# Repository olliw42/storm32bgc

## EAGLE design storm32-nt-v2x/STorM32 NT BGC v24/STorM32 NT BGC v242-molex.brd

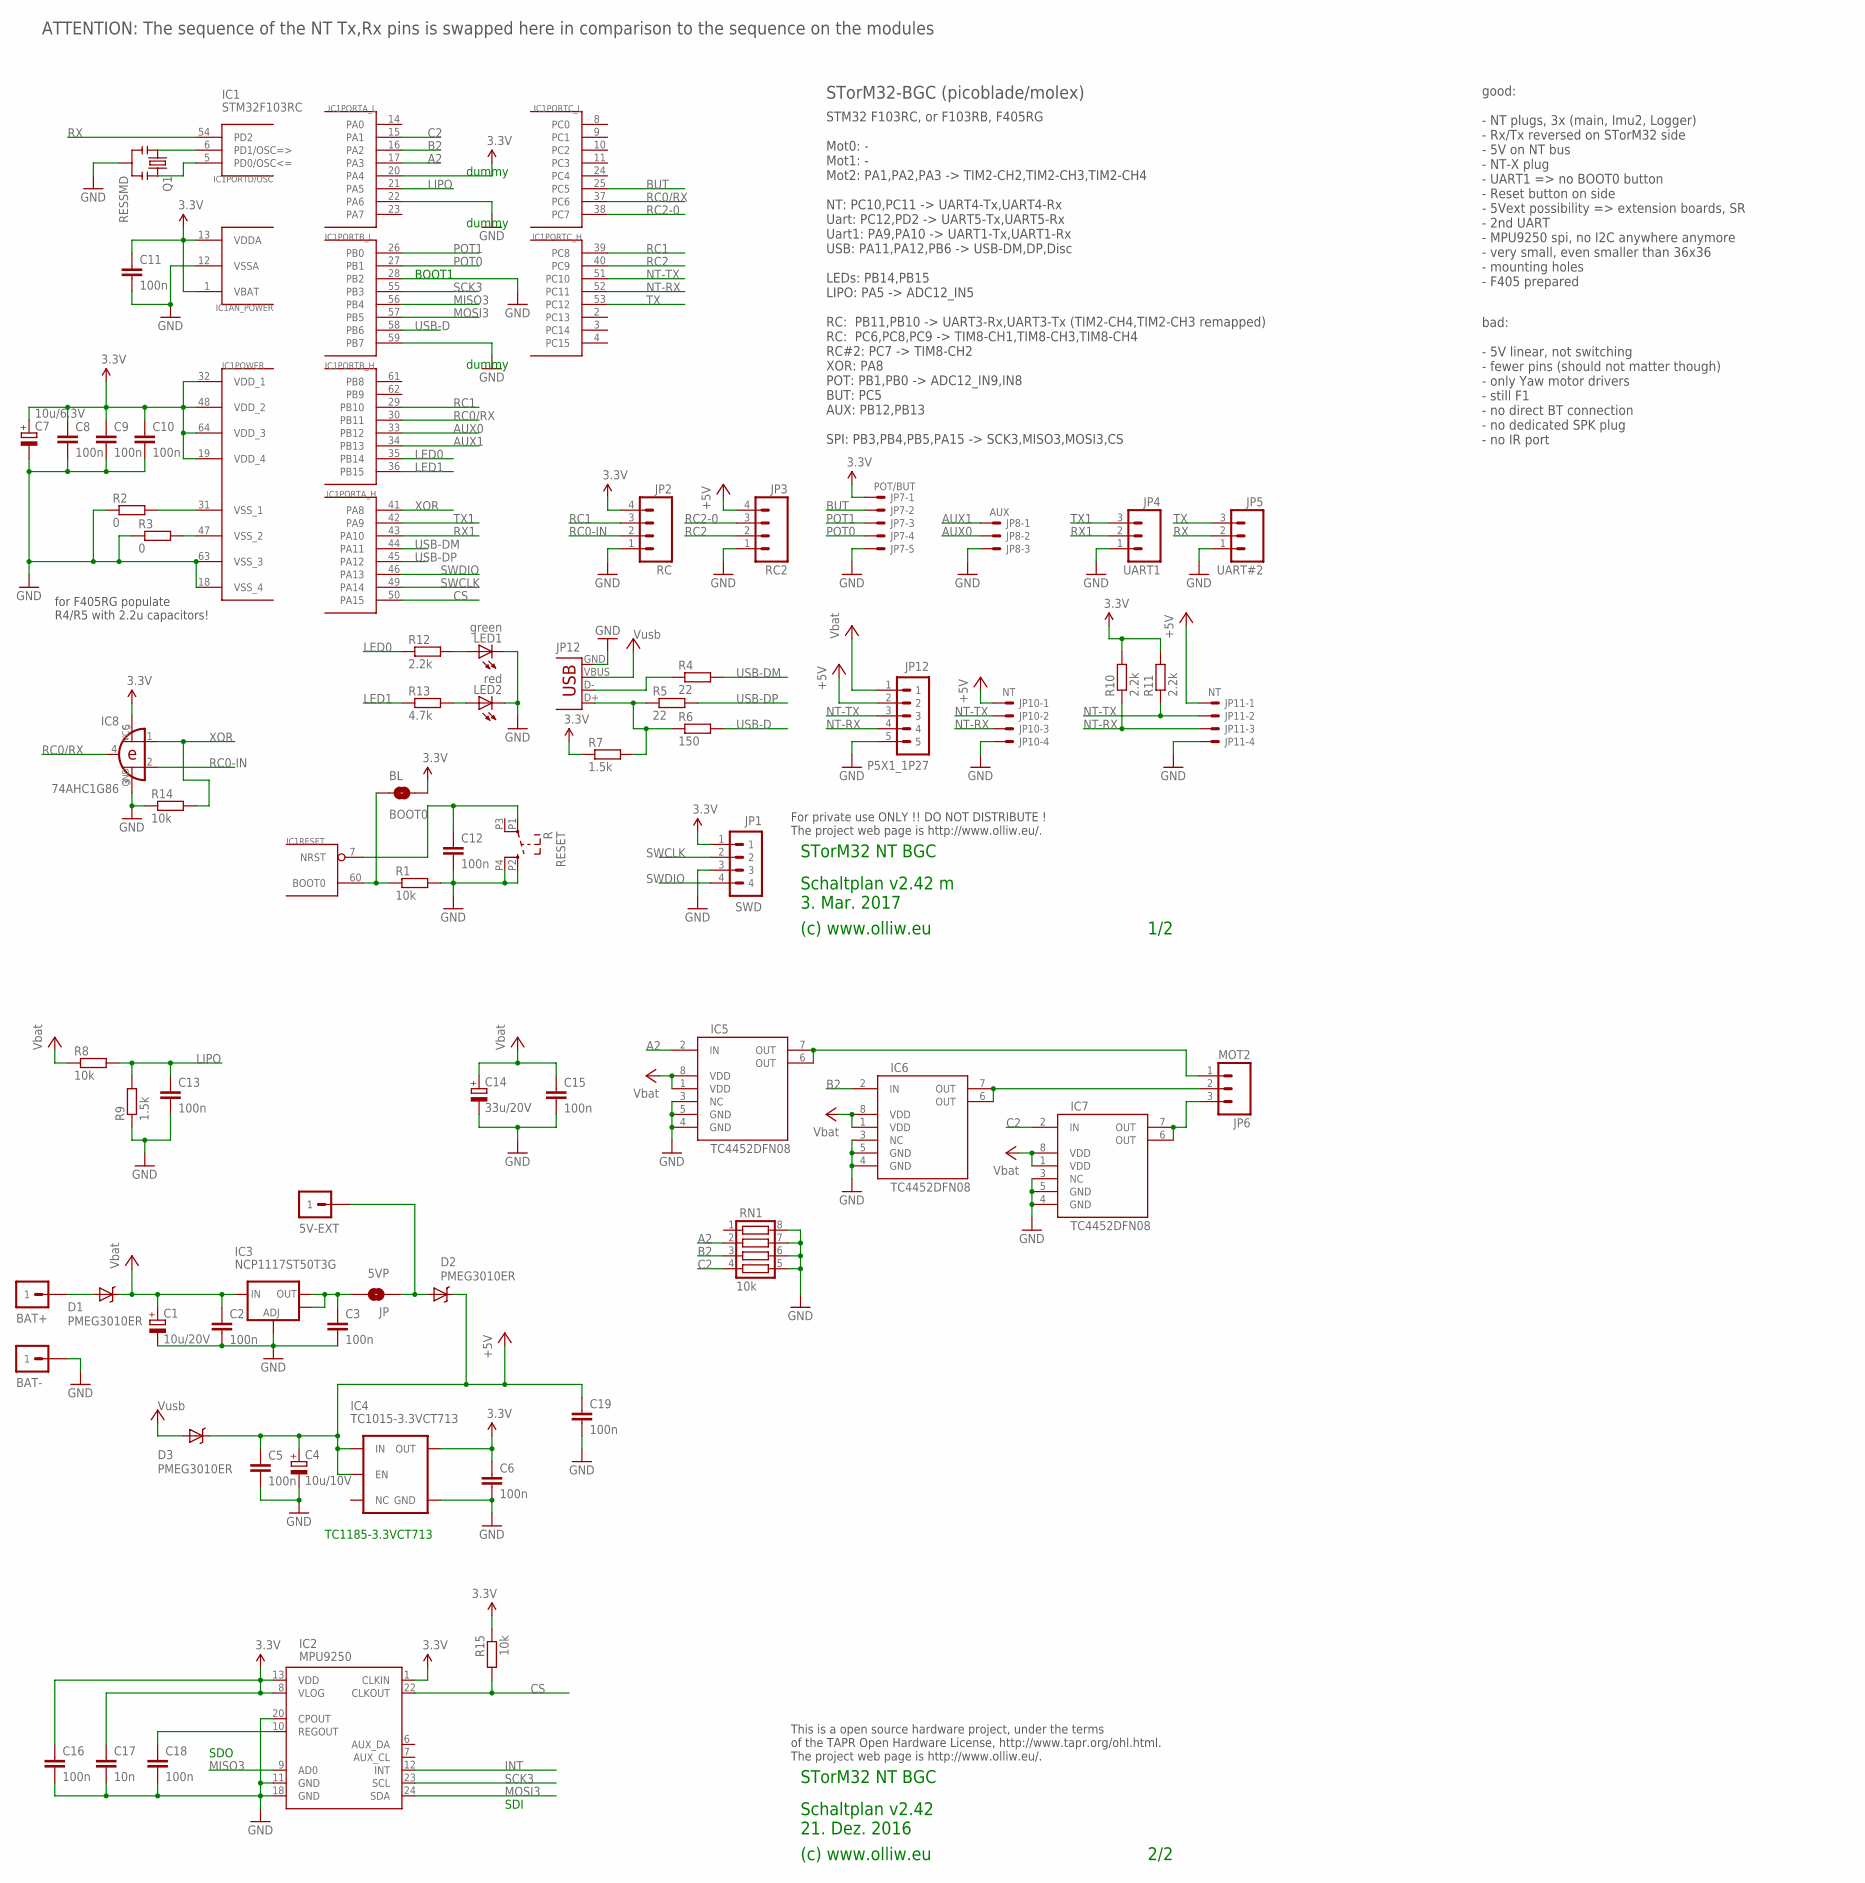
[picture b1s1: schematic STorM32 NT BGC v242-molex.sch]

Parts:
5V-EXT: M1X1; 1X1_WITHOUT
BAT+: M1X1; 1X1_WITHOUT
BAT-: M1X1; 1X1_WITHOUT
BL: BOOT0; SJ_2S-NO
C1: 10u/20V; SMC_B
C2, C5, C15: 100n; C0603
C3, C6, C8, C9, C10, C11, C12, C13, C16, C18, C19: 100n; C0402
C4: 10u/10V; SMC_A
C7: 10u/6.3V; SMC_A
C14: 33u/20V; SMC_C
C17: 10n; C0402
D1, D2, D3: PMEG3010ER; SOD123W-DIODE
IC1: STM32F103RCT6; TQFP64
IC2: MPU9250; QFN-24-3X3
IC3: NCP1117ST50T3G; SOT223
IC4: TC1015-3.3VCT713; SOT23-5
IC5, IC6, IC7: TC4452DFN08; DFN8
IC8: 74AHC1G86; SOT23-5-VER1
JP: 5VP; SJ_2S-NO
JP1: SWD; 4X1_1P27_OCT_BILEX
JP2: RC; 1X04_NO_SILK
JP3: RC2; 1X04_NO_SILK
JP4: UART1; 1X03_NO_SILK
JP5: UART#2; 1X03_NO_SILK
JP6: MOT2; 1X03_NO_SILK
JP7: POT/BUT; SM05B-SRSS-TB
JP8: AUX; SM03B-SRSS-TB
JP10, JP11: NT; SM04B-SRSS-TB
JP12: P5X1_1P27; MOLEX-53261-05-SMD-FLAT
LED1: green; CHIPLED_0603
LED2: red; CHIPLED_0603
Q1: RESSMD; RESONATOR-SMD
R1, R8, R14, R15: 10k; R0402
R2, R3: 0; R0402
R4, R5: 22; R0402
R6: 150; R0402
R7, R9: 1.5k; R0402
R10, R11, R12: 2.2k; R0402
R13: 4.7k; R0402
RESET: R; TACTILE-SWITCH-SMD-RIGHT-TL1014
RN1: 10k; CTS742C083
USB: USB-MICROB

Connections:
3.3V: BL.2, C6.1, C7.+, C8.1, C9.1, C10.1, C11.1, C16.1, C17.1, IC1.1 (VBAT), IC1.13 (VDDA), IC1.19 (VDD_4), IC1.20 (PA4), IC1.32 (VDD_1), IC1.48 (VDD_2), IC1.64 (VDD_3), IC2.1 (CLKIN), IC2.8 (VLOG), IC2.13 (VDD), IC4.5 (OUT), IC8.5 (VCC), JP1.1, JP2.4, JP7.1, R7.1, R10.2, R11.2, R15.1
5V-EXT: 5V-EXT.1, D2.A, JP.1
5V-LDO: C3.1, IC3.2 (OUT), IC3.4 (OUT), JP.2
+5V: C4.+, C5.1, C19.1, D2.C, D3.C, IC4.1 (IN), IC4.3 (EN), JP3.4, JP10.1, JP11.1, JP12.2
A2: IC1.17 (PA3), IC5.2 (IN), RN1.2
AUX0: IC1.33 (PB12), JP8.2
AUX1: IC1.34 (PB13), JP8.1
B2: IC1.16 (PA2), IC6.2 (IN), RN1.3
BATP: BAT+.1, D1.A
BOOT0: BL.1, IC1.60 (BOOT0), R1.1
BUT: IC1.25 (PC5), JP7.2
C2: IC1.15 (PA1), IC7.2 (IN), RN1.4
CS: IC1.50 (PA15), IC2.22 (CLKOUT), R15.2
GND: BAT-.1, C1.-, C2.2, C3.2, C4.-, C5.2, C6.2, C7.-, C8.2, C9.2, C10.2, C11.2, C12.2, C13.2, C14.-, C15.2, C16.2, C17.2, C18.2, C19.2, IC1.12 (VSSA), IC1.18 (VSS_4), IC1.22 (PA6), IC1.28 (PB2), IC1.59 (PB7), IC1.63 (VSS_3), IC2.11 (GND), IC2.18 (GND), IC2.20 (CPOUT), IC3.1 (ADJ), IC4.2 (GND), IC5.3 (NC), IC5.4 (GND), IC5.5 (GND), IC6.3 (NC), IC6.4 (GND), IC6.5 (GND), IC7.3 (NC), IC7.4 (GND), IC7.5 (GND), IC8.3 (GND), JP1.3, JP2.1, JP3.1, JP4.1, JP5.1, JP7.5, JP8.3, JP10.4, JP11.4, JP12.5, LED1.C, LED2.C, Q1.2, R1.2, R2.1, R3.1, R9.1, R14.1, RESET.P2 (1), RESET.P4 (2), RN1.5, RN1.6, RN1.7, RN1.8, USB.GND
INT: IC2.12 (INT)
LED0: IC1.35 (PB14), R12.1
LED1: IC1.36 (PB15), R13.1
LIPO: C13.1, IC1.21 (PA5), R8.2, R9.2
M2A: IC5.6 (OUT), IC5.7 (OUT), JP6.1
M2B: IC6.6 (OUT), IC6.7 (OUT), JP6.2
M2C: IC7.6 (OUT), IC7.7 (OUT), JP6.3
MISO3: IC1.56 (PB4), IC2.9 (AD0)
MOSI3: IC1.57 (PB5), IC2.24 (SDA)
unnamed: C18.1, IC2.10 (REGOUT)
unnamed: LED1.A, R12.2
unnamed: LED2.A, R13.2
unnamed: IC1.47 (VSS_2), R3.2
unnamed: IC1.5 (PD0/OSC<=), Q1.3
unnamed: IC1.6 (PD1/OSC=>), Q1.1
unnamed: R4.1, USB.D-
unnamed: R5.1, R6.1, R7.2, USB.D+
unnamed: IC1.31 (VSS_1), R2.2
NRST: C12.1, IC1.7 (NRST), RESET.P1 (3)
NT-RX: IC1.52 (PC11), JP10.3, JP11.3, JP12.4, R10.1
NT-TX: IC1.51 (PC10), JP10.2, JP11.2, JP12.3, R11.1
POT0: IC1.27 (PB1), JP7.4
POT1: IC1.26 (PB0), JP7.3
RC0-IN: IC8.2 (I1), JP2.2
RC0/RX: IC1.30 (PB11), IC1.37 (PC6), IC8.4 (O)
RC1: IC1.29 (PB10), IC1.39 (PC8), JP2.3
RC2: IC1.40 (PC9), JP3.2
RC2-0: IC1.38 (PC7), JP3.3
RX: IC1.54 (PD2), JP5.2
RX1: IC1.43 (PA10), JP4.2
SCK3: IC1.55 (PB3), IC2.23 (SCL)
SWCLK: IC1.49 (PA14), JP1.2
SWDIO: IC1.46 (PA13), JP1.4
TX: IC1.53 (PC12), JP5.3
TX1: IC1.42 (PA9), JP4.3
USB-D: IC1.58 (PB6), R6.2
USB-DM: IC1.44 (PA11), R4.2
USB-DP: IC1.45 (PA12), R5.2
VCC: C1.+, C2.1, C14.+, C15.1, D1.C, IC3.3 (IN), IC5.1 (VDD), IC5.8 (VDD), IC6.1 (VDD), IC6.8 (VDD), IC7.1 (VDD), IC7.8 (VDD), JP12.1, R8.1
VUSB: D3.A, USB.VBUS
XOR: IC1.41 (PA8), IC8.1 (I0), R14.2

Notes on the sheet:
(c) www.olliw.eu
STorM32 NT BGC
For private use ONLY !! DO NOT DISTRIBUTE ! The project web page is http://www.olliw.eu/.
STM32 F103RC, or F103RB, F405RG Mot0: - Mot1: - Mot2: PA1,PA2,PA3 -> TIM2-CH2,TIM2-CH3,TIM2-CH4 NT: PC10,PC11 -> UART4-Tx,UART4-Rx Uart: PC12,PD2 -> UART5-Tx,UART5-Rx Uart1: PA9,PA10 -> UART1-Tx,UART1-Rx USB: PA11,PA12,PB6 -> USB-DM,DP,Disc LEDs: PB14,PB15 LIPO: PA5 -> ADC12_IN5 RC: PB11,PB10 -> UA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
Schaltplan v2.42 21. Dez. 2016
This is a open source hardware project, under the terms of the TAPR Open Hardware License, http://www.tapr.org/ohl.html. The project web page is http://www.olliw.eu/.
STM32F103RC
STorM32-BGC (picoblade/molex)
for F405RG populate R4/R5 with 2.2u capacitors!
1/2
2/2
IC1
JP12
ATTENTION: The sequence of the NT Tx,Rx pins is swapped here in comparison to the sequence on the modules
SDO
SDI
BOOT1
TC1185-3.3VCT713
good: - NT plugs, 3x (main, Imu2, Logger) - Rx/Tx reversed on STorM32 side - 5V on NT bus - NT-X plug - UART1 => no BOOT0 button - Reset button on side - 5Vext possibility => extension boards, SR - 2nd UART - MPU9250 spi, no I2C anywhere anymore - very small, even smaller than 36x36 - mounting hole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
bad: - 5V linear, not switching - fewer pins (should not matter though) - only Yaw motor drivers - still F1 - no direct BT connection - no dedicated SPK plug - no IR port
dummy
Schaltplan v2.42 m 3. Mar. 2017

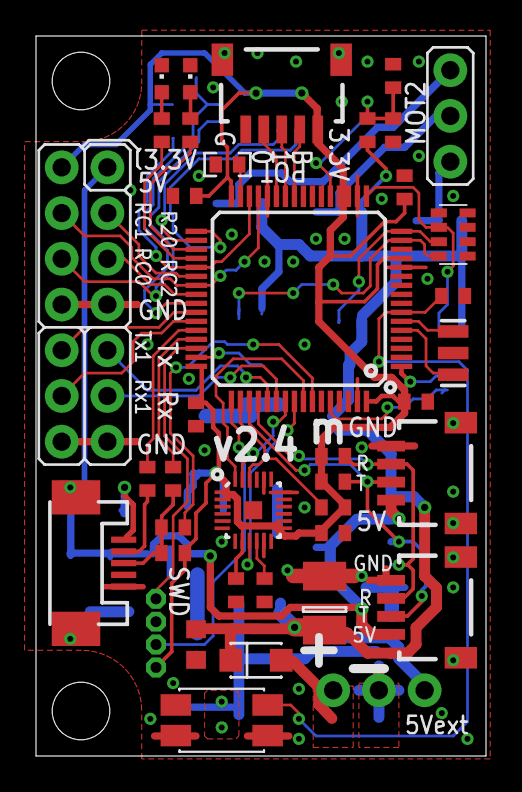
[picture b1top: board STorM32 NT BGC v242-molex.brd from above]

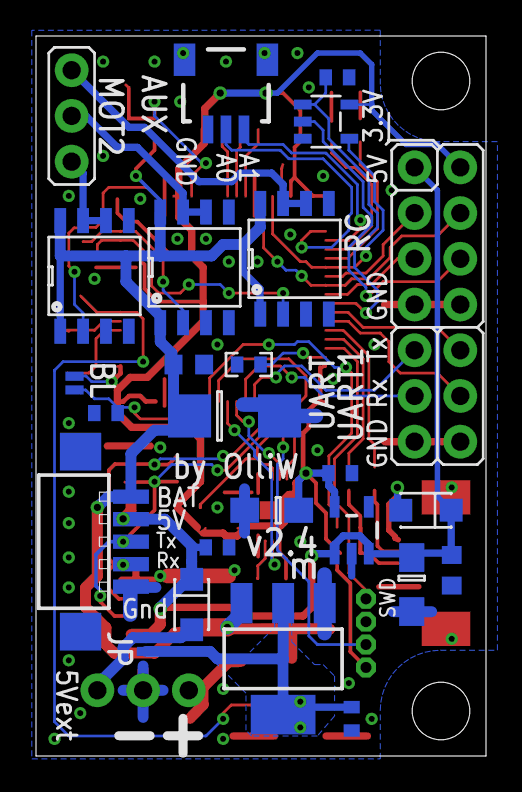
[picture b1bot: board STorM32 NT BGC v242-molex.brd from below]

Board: 2 copper layers, 25.0 x 40.0 mm, 67 parts (23 on the bottom side), 54 nets.

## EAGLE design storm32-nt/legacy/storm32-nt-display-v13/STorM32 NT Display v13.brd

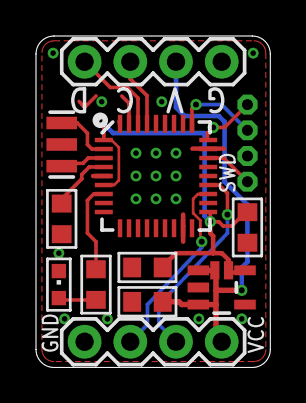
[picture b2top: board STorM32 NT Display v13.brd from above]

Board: 2 copper layers, 13.0 x 18.4 mm, 13 parts (0 on the bottom side), 14 nets.

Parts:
C1, C3, C4: 100n; C0603
C2: 1u; C0603
IC1: STM32F103T8; VFQFPN36
IC2: TC1015-3.3VCT713; SOT23-5
JP1, JP3: 1X04
JP2: SWD; 4X1_1P27_OCT_BILEX
LED1: green; CHIPLED_0603
Q1: CSTCE8M00G55-R0; RESONATOR-SMD
R1: 2.2k; R0603
SJ1: POWER; SJ_2S-NO

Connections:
3.3V: C2.1, C3.1, IC1.1, IC1.6, IC1.19, IC1.27, IC2.5, JP2.1, SJ1.2
5V: C1.1, IC2.1, IC2.3, JP1.1, JP3.3, SJ1.1
GND: C1.2, C2.2, C3.2, C4.2, IC1.5, IC1.17, IC1.18, IC1.24, IC1.26, IC1.29, IC1.32, IC1.35, IC1.36, IC2.2, JP1.4, JP2.3, JP3.4, LED1.C, Q1.2
LED: IC1.7, R1.1
unnamed: C4.1, IC1.4
unnamed: LED1.A, R1.2
unnamed: IC1.2, Q1.1
unnamed: IC1.3, Q1.3
RX: IC1.22, JP1.2
SCL: IC1.33, JP3.2
SDA: IC1.34, JP3.1
SWCLK: IC1.28, JP2.2
SWDIO: IC1.25, JP2.4
TX: IC1.21, JP1.3

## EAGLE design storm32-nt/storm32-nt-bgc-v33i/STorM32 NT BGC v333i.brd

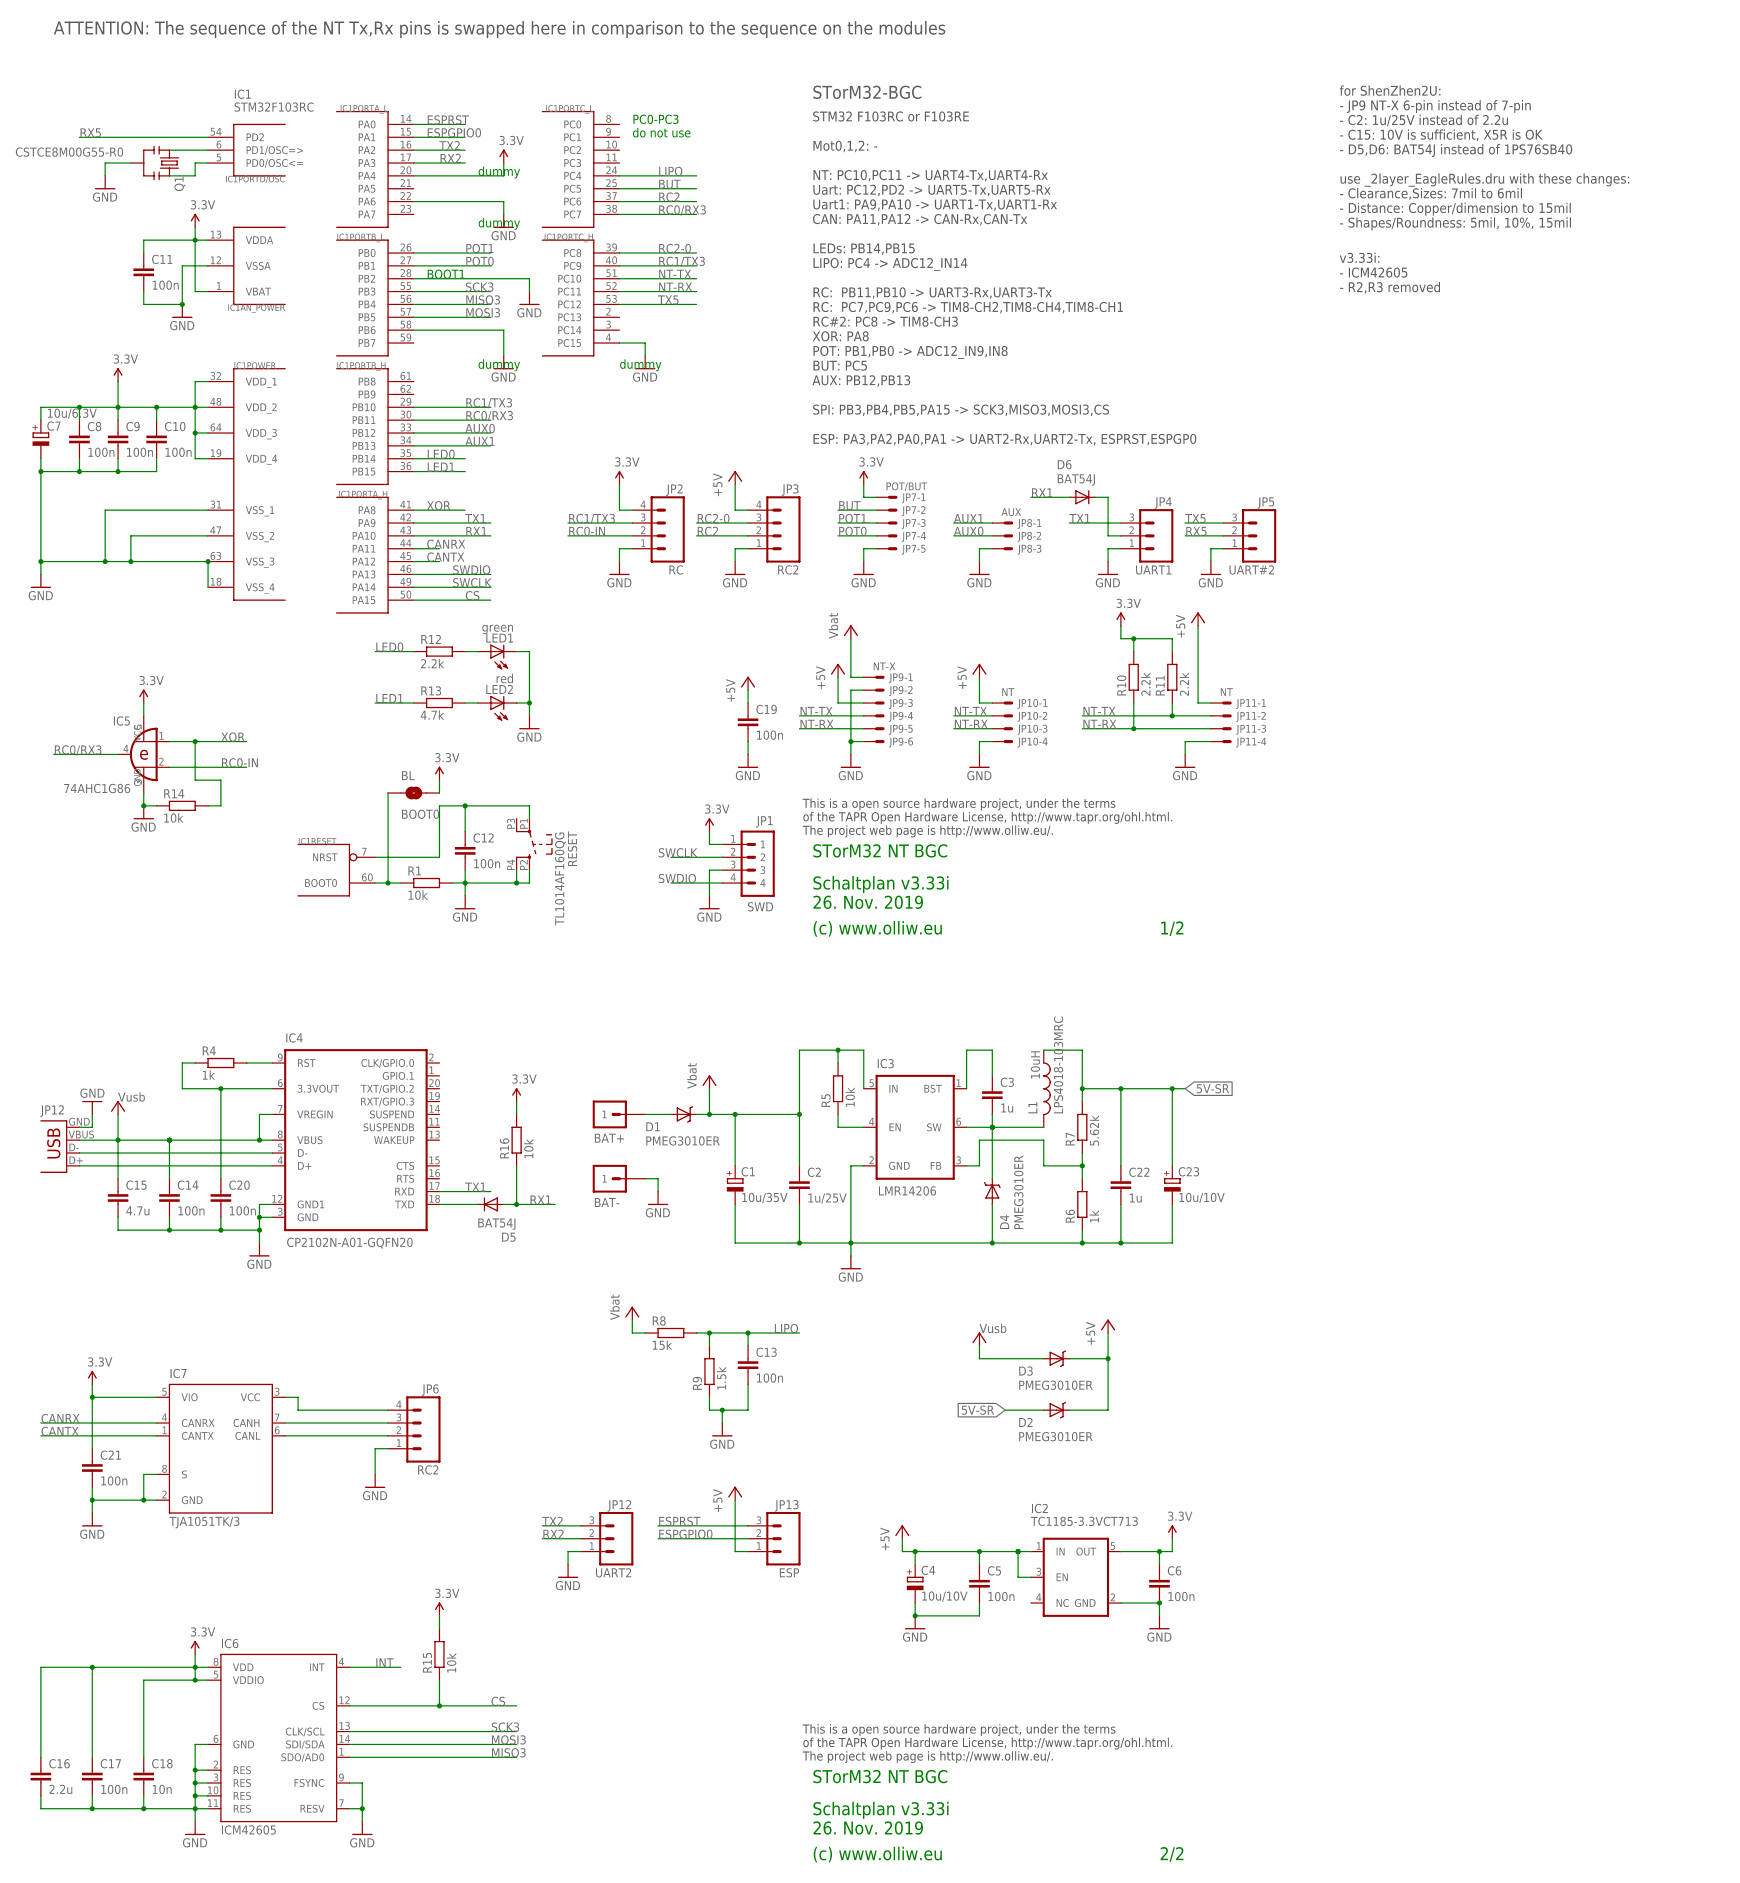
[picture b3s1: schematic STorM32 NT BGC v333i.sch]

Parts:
BAT+: M1X1; 1X1_WITHOUT
BAT-: M1X1; 1X1_WITHOUT
BL: BOOT0; SJ_2S-NO
C1: 10u/35V; SMC_B
C2: 1u/25V; C0603
C3, C22: 1u; C0603
C4, C23: 10u/10V; SMC_A
C5: 100n; C0603
C6, C8, C9, C10, C11, C12, C13, C14, C17, C19, C20, C21: 100n; C0402
C7: 10u/6.3V; SMC_A
C15: 4.7u; C0603
C16: 2.2u; C0603
C18: 10n; C0402
D1, D2, D3, D4: PMEG3010ER; SOD123W-DIODE
D5, D6: BAT54J; SOD110-R
IC1: STM32F103RCT6; TQFP64
IC2: TC1185-3.3VCT713; SOT23-5
IC3: LMR14206; SOT23-6
IC4: CP2102N-A01-GQFN20; QFN20-CP2102N
IC5: 74AHC1G86; SOT23-5-VER1
IC6: ICM42605; LGA14-2.5X3
IC7: TJA1051TK/3; HVSON8
JP1: SWD; 4X1_1P27_OCT_BILEX
JP2: RC; 1X04_NO_SILK
JP3, JP6: RC2; 1X04_NO_SILK
JP4: UART1; 1X03_NO_SILK
JP5: UART#2; 1X03_NO_SILK
JP7: POT/BUT; SM05B-SRSS-TB
JP8: AUX; SM03B-SRSS-TB
JP9: NT-X; SM06B-SRSS-TB
JP10, JP11: NT; SM04B-SRSS-TB
JP12: UART2; 1X03_NO_SILK
JP13: ESP; 1X03_NO_SILK
L1: LPS4018-103MRC; L4X4
LED1: green; CHIPLED_0603
LED2: red; CHIPLED_0603
Q1: CSTCE8M00G55-R0; RESONATOR-SMD
R1, R5, R14, R15, R16: 10k; R0402
R4, R6: 1k; R0402
R7: 5.62k; R0402
R8: 15k; R0402
R9: 1.5k; R0402
R10, R11, R12: 2.2k; R0402
R13: 4.7k; R0402
RESET: TL1014AF160QG; TACTILE-SWITCH-SMD-RIGHT-TL1014
USB: Amphenol 10118192-0001LF; USB-MICROB

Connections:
3.3V: BL.2, C6.1, C7.+, C8.1, C9.1, C10.1, C11.1, C16.1, C17.1, C18.1, C21.1, IC1.1 (VBAT), IC1.13 (VDDA), IC1.19 (VDD_4), IC1.20 (PA4), IC1.32 (VDD_1), IC1.48 (VDD_2), IC1.64 (VDD_3), IC2.5 (OUT), IC5.5 (VCC), IC6.5 (VDDIO), IC6.8 (VDD), IC7.5 (VIO), JP1.1, JP2.4, JP7.1, R10.2, R11.2, R15.2, R16.2
3.3V-CP2102: C20.1, IC4.6 (3.3VOUT), R4.1
5V-CAN-RAW: IC7.3 (VCC), JP6.4
5V-SR: C22.1, C23.+, D2.A, L1.1, R7.2
+5V: C4.+, C5.1, C19.1, D2.C, D3.C, IC2.1 (IN), IC2.3 (EN), JP3.4, JP9.3, JP10.1, JP11.1, JP13.1
AUX0: IC1.33 (PB12), JP8.2
AUX1: IC1.34 (PB13), JP8.1
BATP: BAT+.1, D1.A
BOOT0: BL.1, IC1.60 (BOOT0), R1.1
BUT: IC1.25 (PC5), JP7.2
CANH: IC7.7 (CANH), JP6.3
CANL: IC7.6 (CANL), JP6.2
CANRX: IC1.44 (PA11), IC7.4 (CANRX)
CANTX: IC1.45 (PA12), IC7.1 (CANTX)
CS: IC1.50 (PA15), IC6.12 (CS), R15.1
ESPGPIO0: IC1.15 (PA1), JP13.2
ESPRST: IC1.14 (PA0), JP13.3
GND: BAT-.1, C1.-, C2.2, C4.-, C5.2, C6.2, C7.-, C8.2, C9.2, C10.2, C11.2, C12.2, C13.2, C14.2, C15.2, C16.2, C17.2, C18.2, C19.2, C20.2, C21.2, C22.2, C23.-, D4.A, IC1.4 (PC15), IC1.12 (VSSA), IC1.18 (VSS_4), IC1.22 (PA6), IC1.28 (PB2), IC1.31 (VSS_1), IC1.47 (VSS_2), IC1.58 (PB6), IC1.63 (VSS_3), IC2.2 (GND), IC3.2 (GND), IC4.3 (GND), IC4.12 (GND1), IC5.3 (GND), IC6.2 (RES), IC6.3 (RES), IC6.6 (GND), IC6.7 (RESV), IC6.9 (FSYNC), IC6.10 (RES), IC6.11 (RES), IC7.2 (GND), IC7.8 (S), JP1.3, JP2.1, JP3.1, JP4.1, JP5.1, JP6.1, JP7.5, JP8.3, JP9.2, JP9.6, JP10.4, JP11.4, JP12.1, LED1.C, LED2.C, Q1.2, R1.2, R6.1, R9.1, R14.1, RESET.P2 (1), RESET.P4 (2), USB.GND
INT: IC6.4 (INT)
LED0: IC1.35 (PB14), R12.1
LED1: IC1.36 (PB15), R13.1
LIPO: C13.1, IC1.24 (PC4), R8.2, R9.2
MISO3: IC1.56 (PB4), IC6.1 (SDO/AD0)
MOSI3: IC1.57 (PB5), IC6.14 (SDI/SDA)
unnamed: IC4.5 (D-), USB.D-
unnamed: IC4.4 (D+), USB.D+
unnamed: IC3.4 (EN), R5.1
unnamed: LED1.A, R12.2
unnamed: LED2.A, R13.2
unnamed: IC1.5 (PD0/OSC<=), Q1.3
unnamed: IC1.6 (PD1/OSC=>), Q1.1
unnamed: C3.1, IC3.1 (BST)
unnamed: IC3.3 (FB), R6.2, R7.1
unnamed: C3.2, D4.C, IC3.6 (SW), L1.2
unnamed: D5.C, IC4.18 (TXD)
unnamed: D6.C, JP4.2
unnamed: IC4.9 (RST), R4.2
NRST: C12.1, IC1.7 (NRST), RESET.P1 (3)
NT-RX: IC1.52 (PC11), JP9.5, JP10.3, JP11.3, R10.1
NT-TX: IC1.51 (PC10), JP9.4, JP10.2, JP11.2, R11.1
POT0: IC1.27 (PB1), JP7.4
POT1: IC1.26 (PB0), JP7.3
RC0-IN: IC5.2 (I1), JP2.2
RC0/RX3: IC1.30 (PB11), IC1.38 (PC7), IC5.4 (O)
RC1/TX3: IC1.29 (PB10), IC1.40 (PC9), JP2.3
RC2: IC1.37 (PC6), JP3.2
RC2-0: IC1.39 (PC8), JP3.3
RX1: D5.A, D6.A, IC1.43 (PA10), R16.1
RX2: IC1.17 (PA3), JP12.2
RX5: IC1.54 (PD2), JP5.2
SCK3: IC1.55 (PB3), IC6.13 (CLK/SCL)
SWCLK: IC1.49 (PA14), JP1.2
SWDIO: IC1.46 (PA13), JP1.4
TX1: IC1.42 (PA9), IC4.17 (RXD), JP4.3
TX2: IC1.16 (PA2), JP12.3
TX5: IC1.53 (PC12), JP5.3
VCC: C1.+, C2.1, D1.C, IC3.5 (IN), JP9.1, R5.2, R8.1
VUSB: C14.1, C15.1, D3.A, IC4.7 (VREGIN), IC4.8 (VBUS), USB.VBUS
XOR: IC1.41 (PA8), IC5.1 (I0), R14.2

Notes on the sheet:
(c) www.olliw.eu
STorM32 NT BGC
This is a open source hardware project, under the terms of the TAPR Open Hardware License, http://www.tapr.org/ohl.html. The project web page is http://www.olliw.eu/.
STM32 F103RC or F103RE Mot0,1,2: - NT: PC10,PC11 -> UART4-Tx,UART4-Rx Uart: PC12,PD2 -> UART5-Tx,UART5-Rx Uart1: PA9,PA10 -> UART1-Tx,UART1-Rx CAN: PA11,PA12 -> CAN-Rx,CAN-Tx LEDs: PB14,PB15 LIPO: PC4 -> ADC12_IN14 RC: PB11,PB10 -> UART3-Rx,UART3-Tx RC: PC7,PC9,PC6 -> TIM8-CH2,TIM8-CH4,TIM8-CH1 RC#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
Schaltplan v3.33i 26. Nov. 2019
STM32F103RC
STorM32-BGC
1/2
2/2
IC1
JP12
ATTENTION: The sequence of the NT Tx,Rx pins is swapped here in comparison to the sequence on the modules
BOOT1
dummy
10uH
PC0-PC3 do not use
for ShenZhen2U: - JP9 NT-X 6-pin instead of 7-pin - C2: 1u/25V instead of 2.2u - C15: 10V is sufficient, X5R is OK - D5,D6: BAT54J instead of 1PS76SB40 use _2layer_EagleRules.dru with these changes: - Clearance,Sizes: 7mil to 6mil - Distance: Copper/dimension to 15mil - Shapes/Roundness: 5mil, 10%,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
v3.33i: - ICM42605 - R2,R3 removed

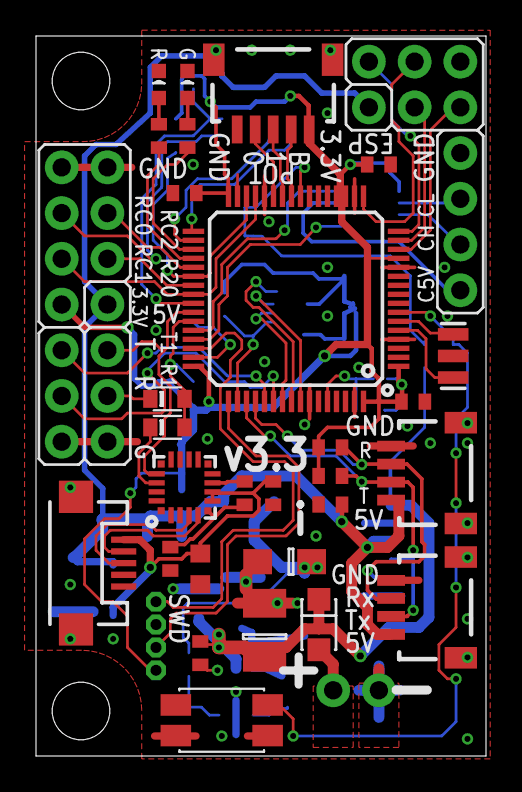
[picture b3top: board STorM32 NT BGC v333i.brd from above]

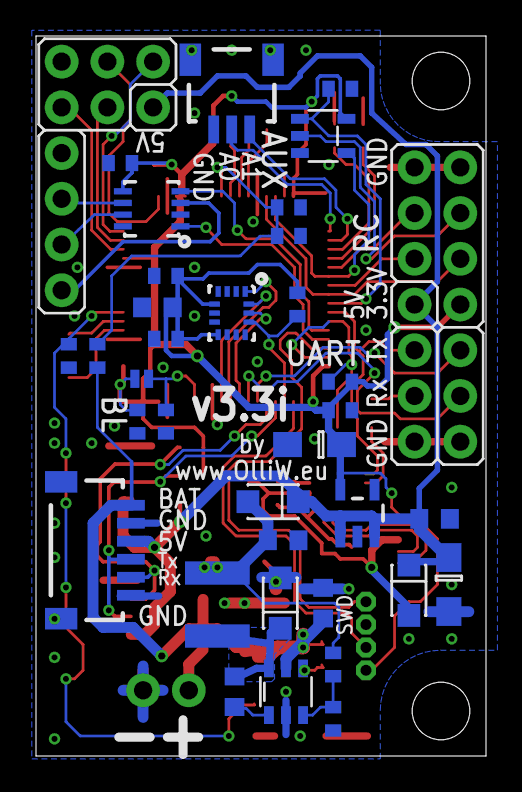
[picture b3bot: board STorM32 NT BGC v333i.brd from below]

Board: 2 copper layers, 25.0 x 40.0 mm, 72 parts (34 on the bottom side), 58 nets.

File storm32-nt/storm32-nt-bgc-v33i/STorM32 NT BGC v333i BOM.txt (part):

Stückliste exportiert aus C:/Users/Olli/Documents/GitHub/storm32bgc/storm32-nt/storm32-nt-bgc-v33i/STorM32 NT BGC v333i.sch am 23.05.2020 11:32

Part  Value                    Device                  Package                         Description                                                 
BAT+                           M1X1                    1X1_WITHOUT                                                                                 
BAT-                           M1X1                    1X1_WITHOUT                                                                                 
BL    BOOT0                    SOLDERJUMPERNO          SJ_2S-NO                        Solder Jumper                                               
C1    10u/35V                  CPOL-EUSMCB             SMC_B                           POLARIZED CAPACITOR, European symbol                        
C2    1u/25V                   C-EUC0603               C0603                           CAPACITOR, European symbol                                  
C3    1u                       C-EUC0603               C0603                           CAPACITOR, European symbol                                  
C4    10u/10V                  CPOL-EUSMCA             SMC_A                           POLARIZED CAPACITOR, European symbol                        
C5    100n                     C-EUC0603               C0603                           CAPACITOR, European symbol                                  
C6    100n                     C-EUC0402               C0402                           CAPACITOR, European symbol                                  
C7    10u/6.3V                 CPOL-EUSMCA             SMC_A                           POLARIZED CAPACITOR, European symbol                        
C8    100n                     C-EUC0402               C0402                           CAPACITOR, European symbol                                  
C9    100n                     C-EUC0402               C0402                           CAPACITOR, European symbol                                  
C10   100n                     C-EUC0402               C0402                           CAPACITOR, European symbol                                  
C11   100n                     C-EUC0402               C0402                           CAPACITOR, European symbol                                  
C12   100n                     C-EUC0402               C0402                           CAPACITOR, European symbol                                  
C13   100n                     C-EUC0402               C0402                           CAPACITOR, European symbol                                  
C14   100n                     C-EUC0402               C0402                           CAPACITOR, European symbol                                  
C15   4.7u                     C-EUC0603               C0603                           CAPACITOR, European symbol                                  
C16   2.2u                     C-EUC0603               C0603                           CAPACITOR, European symbol                                  
C17   100n                     C-EUC0402               C0402                           CAPACITOR, European symbol                                  
C18   10n                      C-EUC0402               C0402                           CAPACITOR, European symbol                                  
C19   100n                     C-EUC0402               C0402                           CAPACITOR, European symbol                                  
C20   100n                     C-EUC0402               C0402                           CAPACITOR, European symbol                                  
C21   100n                     C-EUC0402               C0402                           CAPACITOR, European symbol                                  
C22   1u                       C-EUC0603               C0603                           CAPACITOR, European symbol                                  
C23   10u/10V                  CPOL-EUSMCA             SMC_A                           POLARIZED CAPACITOR, European symbol                        
D1    PMEG3010ER               DIODE-SCHOTTKYSOD123-W  SOD123W-DIODE                                                                               
D2    PMEG3010ER               DIODE-SCHOTTKYSOD123-W  SOD123W-DIODE                                                                               
D3    PMEG3010ER               DIODE-SCHOTTKYSOD123-W  SOD123W-DIODE                                                                               
D4    PMEG3010ER               DIODE-SCHOTTKYSOD123-W  SOD123W-DIODE                                                                               
D5    BAT54J                   DIODE-SOD110-R          SOD110-R                        DIODE                                                       
D6    BAT54J                   DIODE-SOD110-R          SOD110-R                        DIODE                                                       
IC1   STM32F103RCT6            STM32F10XRXT6           TQFP64                          STM32F101/103 64pin LQFP                                    
IC2   TC1185-3.3VCT713         V_REG_TPS76433SOT23-5   SOT23-5                         Voltage Regulator                                           
IC3   LMR14206                 MP2359                  SOT23-6                                                                                     
IC4   CP2102N-A01-GQFN20       CP2102N-QFN20           QFN20-CP2102N                                                                               
IC5   74AHC1G86                74AHC1G86               SOT23-5-VER1                                                                                
IC6   ICM42605                 ICM42605                LGA14-2.5X3                                                                                 
IC7   TJA1051TK/3              TJA1051TK/3             HVSON8                                                                                      
JP1   SWD                      P4X1_1P27-OCT_BILEX     4X1_1P27_OCT_BILEX                                                                          
JP2   RC                       M041X04_NO_SILK         1X04_NO_SILK                    Header 4                                                    
JP3   RC2                      M041X04_NO_SILK         1X04_NO_SILK                    Header 4                                                    
JP4   UART1                    M031X03_NO_SILK         1X03_NO_SILK                    Header 3                                                    
JP5   UART#2                   M031X03_NO_SILK         1X03_NO_SILK                    Header 3                                                    
JP6   RC2                      M041X04_NO_SILK         1X04_NO_SILK                    Header 4                                                    
JP7   POT/BUT                  SM05B-SRSS-TB           SM05B-SRSS-TB                   Disconnectable Crimp style connector, 1.0mm pitch5 contacts 
JP8   AUX                      SM03B-SRSS-TB           SM03B-SRSS-TB                   Disconnectable Crimp style connector, 1.0mm pitch3 contacts 
JP9   NT-X                     SM06B-SRSS-TB           SM06B-SRSS-TB                   Disconnectable Crimp style connector, 1.0mm pitch6 contacts 
JP10  NT                       SM04B-SRSS-TB           SM04B-SRSS-TB                   Disconnectable Crimp style connector, 1.0mm pitch4 contacts 
JP11  NT                       SM04B-SRSS-TB           SM04B-SRSS-TB                   Disconnectable Crimp style connector, 1.0mm pitch4 contacts 
JP12  UART2                    M031X03_NO_SILK         1X03_NO_SILK                    Header 3                                                    
JP13  ESP                      M031X03_NO_SILK         1X03_NO_SILK                    Header 3                                                    
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

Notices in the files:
parts and their libraries:
Licensing: CC v3.0 Share-Alike You are welcome to use this library for commercial purposes.
